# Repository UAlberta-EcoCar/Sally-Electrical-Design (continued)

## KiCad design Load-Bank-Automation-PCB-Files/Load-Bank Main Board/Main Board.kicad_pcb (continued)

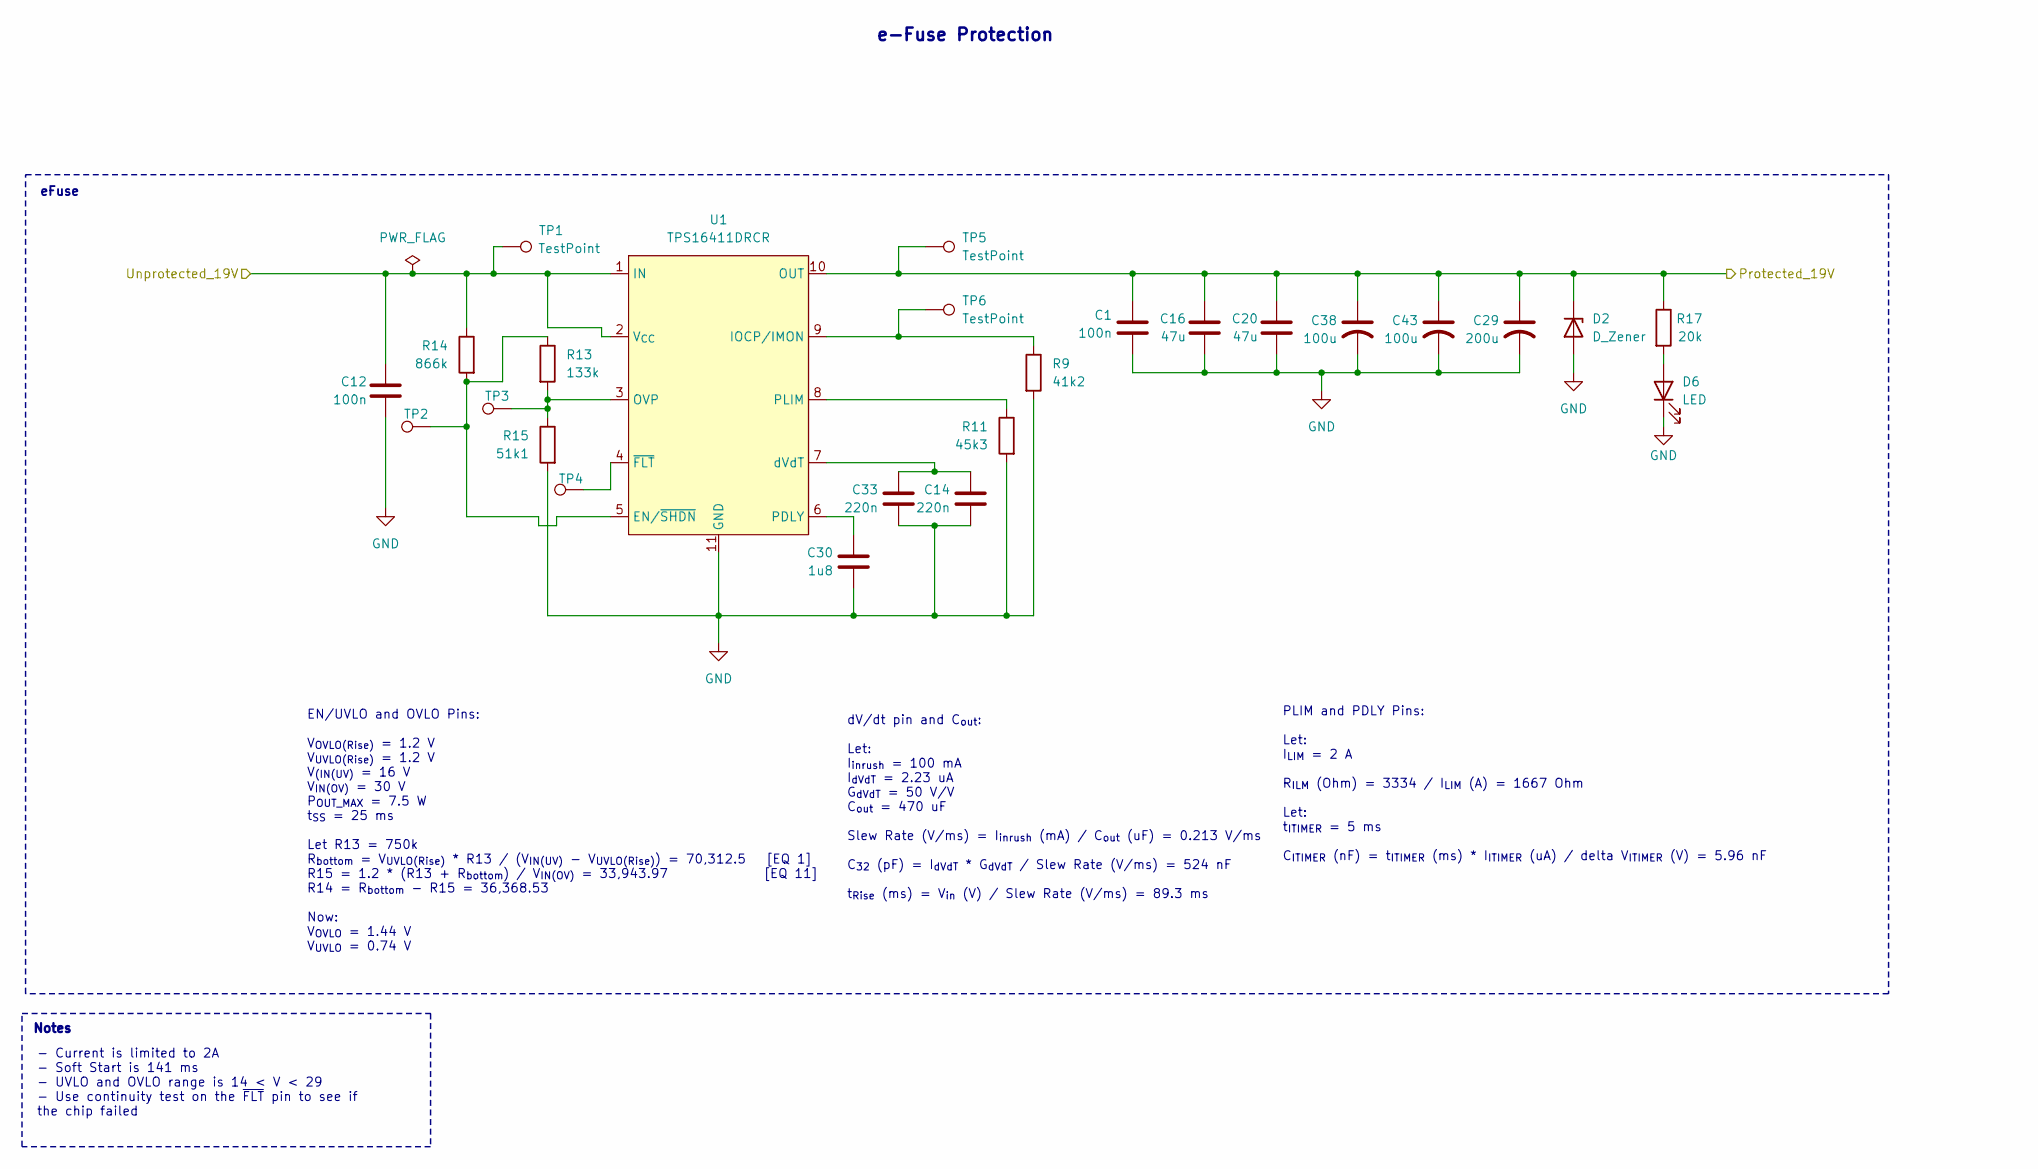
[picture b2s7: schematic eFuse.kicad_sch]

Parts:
C1, C12: 100n; C_0603_1608Metric_Pad1.08x0.95mm_HandSolder
C14, C33: 220n; C_0603_1608Metric_Pad1.08x0.95mm_HandSolder
C16, C20: 47u; C_1206_3216Metric_Pad1.33x1.80mm_HandSolder
C29: 200u; CP_Radial_D8.0mm_P3.50mm
C30: 1u8; C_1206_3216Metric_Pad1.33x1.80mm_HandSolder
C38, C43: 100u; CP_Radial_D8.0mm_P3.50mm
D2: D_Zener; D_TUMD2
D6: LED; LED_0603_1608Metric
R9: 41k2; R_0603_1608Metric_Pad0.98x0.95mm_HandSolder
R11: 45k3; R_0603_1608Metric_Pad0.98x0.95mm_HandSolder
R13: 133k; R_0603_1608Metric_Pad0.98x0.95mm_HandSolder
R14: 866k; R_0603_1608Metric_Pad0.98x0.95mm_HandSolder
R15: 51k1; R_0603_1608Metric_Pad0.98x0.95mm_HandSolder
R17: 20k; R_0603_1608Metric_Pad0.98x0.95mm_HandSolder
TP1, TP2, TP3, TP4, TP5, TP6: TestPoint; TestPoint_Pad_D1.0mm
U1: TPS16411DRCR; VSON-10-1EP_3x3mm_P0.5mm_EP1.65x2.4mm_ThermalVias

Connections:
/Main_Power/DC-DC Buck 12V/Protected_19V: C1.1, C16.1, C20.1, C29.1, C38.1, C43.1, D2.1 (K), R17.1, TP5.1, U1.10 (OUT); also elsewhere on the board
/Main_Power/eFuse/Unprotected_19V: C12.1, R14.1, TP1.1, U1.1 (IN), U1.2 (V_{CC}); also elsewhere on the board
GND: C1.2, C12.2, C14.1, C16.2, C20.2, C29.2, C30.1, C33.1, C38.2, C43.2, D2.2 (A), D6.1 (K), R9.2, R11.2, R15.2, U1.11 (GND); also elsewhere on the board
unnamed: D6.2 (A), R17.2
unnamed: R13.1, R14.2, TP2.1, U1.5 (EN/~SHDN)
unnamed: R9.1, TP6.1, U1.9 (IOCP/IMON)
unnamed: R13.2, R15.1, TP3.1, U1.3 (OVP)
unnamed: C30.2, U1.6 (PDLY)
unnamed: R11.1, U1.8 (PLIM)
unnamed: C14.2, C33.2, U1.7 (dVdT)
unnamed: TP4.1, U1.4 (~FLT)

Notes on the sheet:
PLIM and PDLY Pins: Let: I_{LIM} = 2 A R_{ILM} (Ohm) = 3334 / I_{LIM} (A) = 1667 Ohm Let: t_{ITIMER} = 5 ms C_{ITIMER} (nF) = t_{ITIMER} (ms) * I_{ITIMER} (uA) / delta V_{ITIMER} (V) = 5.96 nF
Notes
EN/UVLO and OVLO Pins: V_{OVLO(Rise)} = 1.2 V V_{UVLO(Rise)} = 1.2 V V_{(IN(UV)} = 16 V V_{IN(OV)} = 30 V P_{OUT_MAX} = 7.5 W t_{SS} = 25 ms Let R13 = 750k R_{bottom} = V_{UVLO(Rise)} * R13 / (V_{IN(UV)} - V_{UVLO(Rise)}) = 70,312.5 [EQ 1] R15 = 1.2 * (R13 + R_{bottom}) / V_{IN(OV)} = 33,943.97 [EQ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
e-Fuse Protection
- Current is limited to 2A - Soft Start is 141 ms - UVLO and OVLO range is 14 < V < 29 - Use continuity test on the ~{FLT} pin to see if the chip failed
eFuse
dV/dt pin and C_{out}: Let: I_{inrush} = 100 mA I_{dVdT} = 2.23 uA G_{dVdT} = 50 V/V C_{out} = 470 uF Slew Rate (V/ms) = I_{inrush} (mA) / C_{out} (uF) = 0.213 V/ms C_{32} (pF) = I_{dVdT} * G_{dVdT} / Slew Rate (V/ms) = 524 nF t_{Rise} (ms) = V_{in} (V) / Slew Rate (V/ms) = 89.3 ms

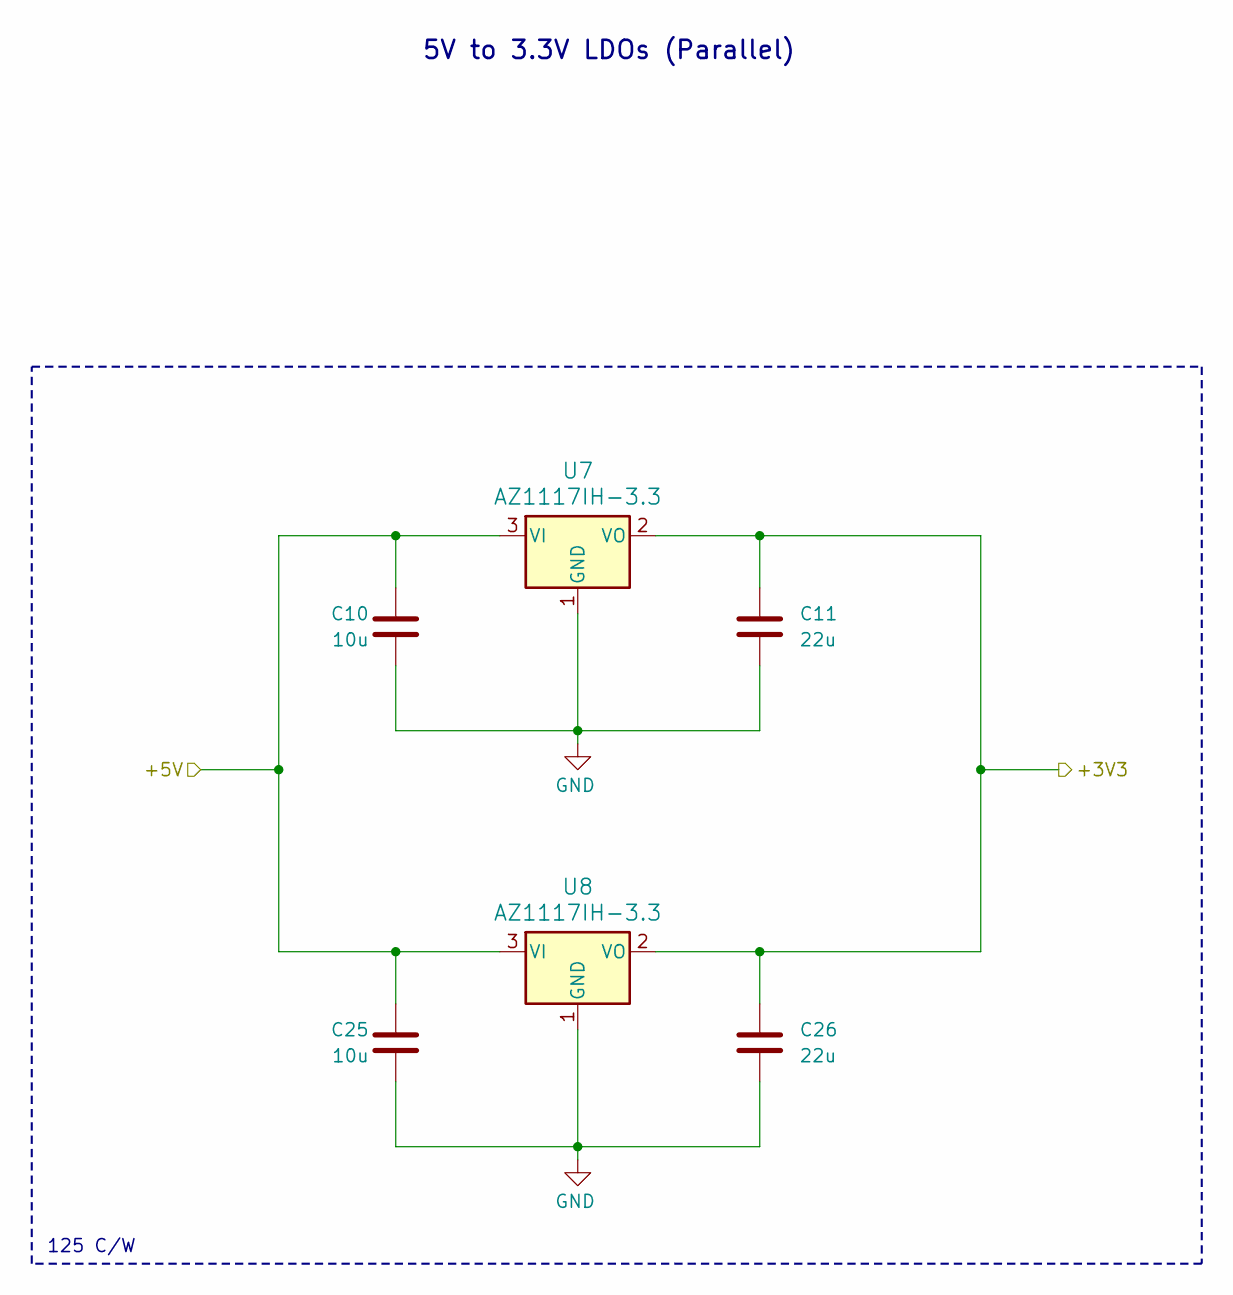
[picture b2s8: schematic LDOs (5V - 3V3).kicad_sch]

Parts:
C10, C25: 10u; C_1206_3216Metric_Pad1.33x1.80mm_HandSolder
C11, C26: 22u; C_0805_2012Metric_Pad1.18x1.45mm_HandSolder
U7, U8: AZ1117IH-3.3; SOT-223-3_TabPin2

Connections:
+5V: C10.1, C25.1, U7.3 (VI), U8.3 (VI); also elsewhere on the board
GND: C10.2, C11.2, C25.2, C26.2, U7.1 (GND), U8.1 (GND); also elsewhere on the board

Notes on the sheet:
5V to 3.3V LDOs (Parallel)
125 C/W

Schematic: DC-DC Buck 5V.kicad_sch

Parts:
C3: 3u3; C_0805_2012Metric_Pad1.18x1.45mm_HandSolder
C21, C27: 100n; C_0603_1608Metric_Pad1.08x0.95mm_HandSolder
C28: 15u; C_1210_3225Metric_Pad1.33x2.70mm_HandSolder
L2: 8u2; L_Bourns_SDR0403
R4: 750k; R_0402_1005Metric_Pad0.72x0.64mm_HandSolder
R20: 294k; R_0402_1005Metric_Pad0.72x0.64mm_HandSolder
R29: 88.7k; R_0402_1005Metric_Pad0.72x0.64mm_HandSolder
R30: 22.1k; R_0402_1005Metric_Pad0.72x0.64mm_HandSolder
TP9, TP10: TestPoint; TestPoint_Pad_D1.0mm
U4: TPS560430YQDBVRQ1; SOT-23-6

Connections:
+5V: C28.1, L2.2, R29.1, TP10.1; also elsewhere on the board
+12V: C3.1, C21.1, R4.1, U4.5 (VIN); also elsewhere on the board
GND: C3.2, C21.2, C28.2, R20.2, R30.2, U4.2 (GND); also elsewhere on the board
unnamed: C27.1, U4.1 (CB)
unnamed: R4.2, R20.1, TP9.1, U4.4 (EN)
unnamed: R29.2, R30.1, U4.3 (FB)
unnamed: C27.2, L2.1, U4.6 (SW)

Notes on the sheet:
https://webench.ti.com/appinfo/webench/scripts/SDP.cgi?ID=B7009E65DFD8AE3E
DC/DC Buck Converter
Notes
Did many caluclations by hand and confirms some values
PFM Buck Converter
V_{IN_MAX} = 36 V I_{OUT_MAX} = 600 mA t_{SS} = 1.8 ms f_{sw} = 2100 KHz

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
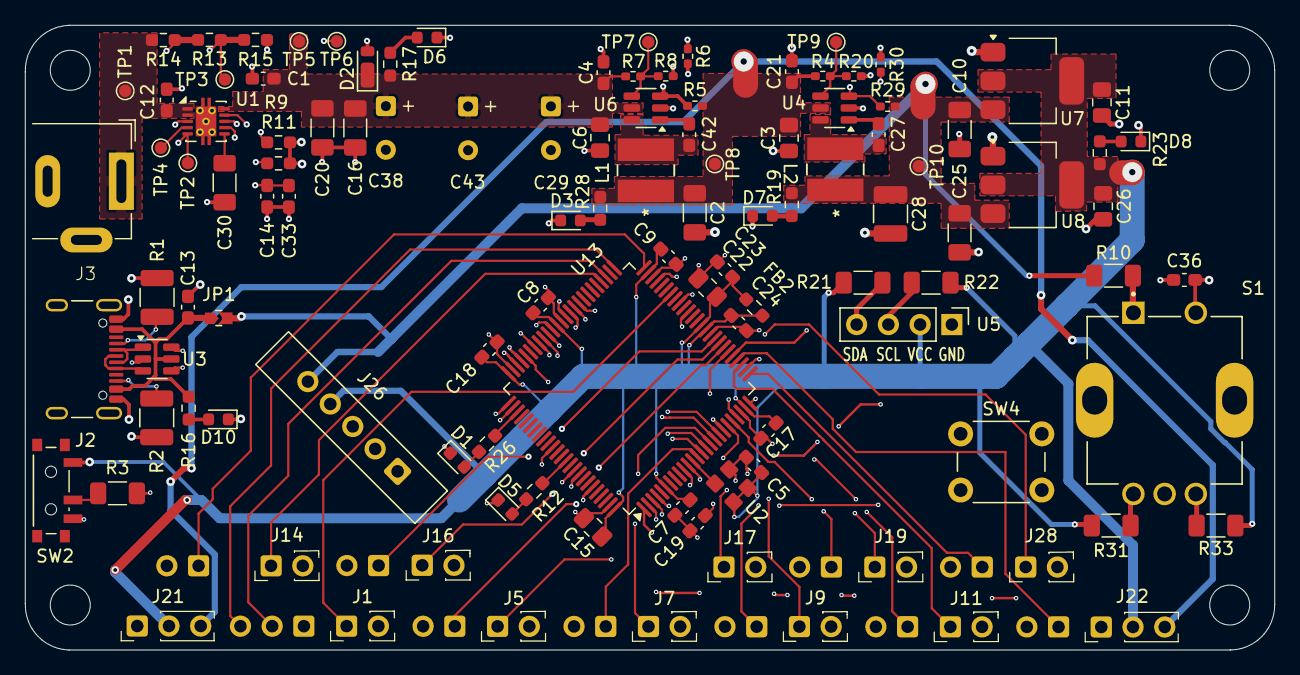
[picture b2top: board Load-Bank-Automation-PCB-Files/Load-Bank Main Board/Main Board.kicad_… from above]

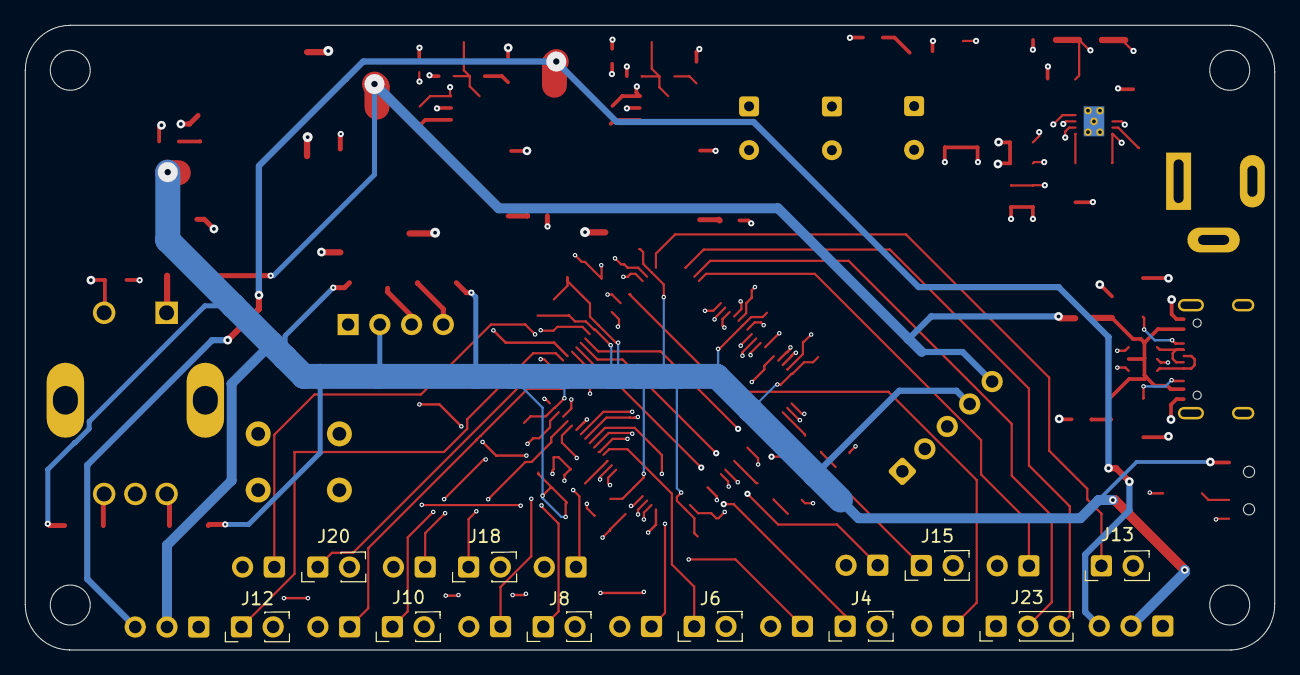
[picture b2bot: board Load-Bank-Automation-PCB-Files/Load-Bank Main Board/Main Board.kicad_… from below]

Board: 4 copper layers, 100.0 x 50.0 mm, 126 parts (10 on the bottom side), 90 nets.

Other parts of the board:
D7, D8: LED; LED_0603_1608Metric
JP1: Jumper_2_Open; J_0603_Triangular
R19, R23: 20k; R_0603_1608Metric_Pad0.98x0.95mm_HandSolder

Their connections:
+5V: JP1.2 (B), R19.2; also elsewhere on the board
GND: D7.1 (K), D8.1 (K); also elsewhere on the board
unnamed: D7.2 (A), R19.1
unnamed: D8.2 (A), R23.1
VBUS: JP1.1 (A); also elsewhere on the board

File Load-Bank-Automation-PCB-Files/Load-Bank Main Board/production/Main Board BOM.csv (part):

"Reference","Qty","Value","DNP","Exclude from BOM","Exclude from Board","Footprint","Datasheet","Description"
"C1,C4,C5,C7,C8,C9,C12,C13,C17,C18,C19,C21,C23,C24,C27,C36,C42","17","100n","","","","Capacitor_SMD:C_0603_1608Metric_Pad1.08x0.95mm_HandSolder","https://www.digikey.ca/en/products/detail/tdk-corporation/CG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","Unpolarized capacitor"
"C2","1","15u","","","","Capacitor_SMD:C_1206_3216Metric_Pad1.33x1.80mm_HandSolder","https://www.digikey.ca/en/products/detail/tdk-corporation/C3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","Unpolarized capacitor"
"C3,C6","2","3u3","","","","Capacitor_SMD:C_0805_2012Metric_Pad1.18x1.45mm_HandSolder","https://www.digikey.ca/en/products/detail/tdk-corporation/C2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","C2012X7R1V335K125AC,Unpolarized capacitor"
"C10,C25","2","10u","","","","Capacitor_SMD:C_1206_3216Metric_Pad1.33x1.80mm_HandSolder","https://www.digikey.ca/en/products/detail/tdk-corporation/C2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","C2012X5R1C106K085AC"
"C11,C26","2","22u","","","","Capacitor_SMD:C_0805_2012Metric_Pad1.18x1.45mm_HandSolder","https://www.digikey.ca/en/products/detail/nic-components-cor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","NMC0805X5R226M25TRPLPF"
"C14,C33","2","220n","","","","Capacitor_SMD:C_0603_1608Metric_Pad1.08x0.95mm_HandSolder","https://www.digikey.ca/en/products/detail/samsung-electro-me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","CL10B224KB8NNNC"
"C15,C22","2","10u","","","","Capacitor_SMD:C_0805_2012Metric_Pad1.18x1.45mm_HandSolder","https://www.digikey.ca/en/products/detail/samsung-electro-me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","Unpolarized capacitor"
"C16,C20","2","47u","","","","Capacitor_SMD:C_1206_3216Metric_Pad1.33x1.80mm_HandSolder","https://www.digikey.ca/en/products/detail/tdk-corporation/C3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","Unpolarized capacitor"
"C28","1","15u","","","","Capacitor_SMD:C_1210_3225Metric_Pad1.33x2.70mm_HandSolder","https://www.digikey.ca/en/products/detail/tdk-corporation/C3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","Unpolarized capacitor"
"C29","1","200u","","","","Capacitor_THT:CP_Radial_D8.0mm_P3.50mm","https://www.digikey.ca/en/products/detail/rubycon/35ZLH220ME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","capacitor, US symbol"
"C30","1","1u8","","","","Capacitor_SMD:C_1206_3216Metric_Pad1.33x1.80mm_HandSolder","https://www.digikey.ca/en/products/detail/kemet/C1206C185K5R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","C1206C185K5RACAUTO"
"C38,C43","2","100u","","","","Capacitor_THT:CP_Radial_D8.0mm_P3.50mm","https://www.digikey.ca/en/products/detail/nichicon/UVR1H101M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","capacitor, US symbol"
"D1,D3,D5,D6,D7,D8,D10","7","LED","","","","LED_SMD:LED_0603_1608Metric","~","Light emitting diode"
"D2","1","D_Zener","","","","Diode_SMD:D_TUMD2","https://toshiba.semicon-storage.com/info/CUHZ24V_datasheet_e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","VBR = 24 (Typ), VC = 25.5"
"FB2","1","300R","","","","Resistor_SMD:R_0603_1608Metric_Pad0.98x0.95mm_HandSolder","https://www.digikey.ca/en/products/detail/bourns-inc/MU3261-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","Ferrite bead"
"H1,H2,H3,H4","4","MountingHole","","Excluded from BOM","","MountingHole:MountingHole_3.2mm_M3","~","Mounting Hole without connection"
"J1,J4,J5,J6,J7,J8,J9,J10,J11,J12,J13,J14,J15,J16,J17,J18,J19,J20,J28","19","Conn_01x02","","","","Connector_PinHeader_1.00mm:IDC_PinHeader_1x02_P1.00mm_Vertical","~","Generic connector, single row, 01x02, script generated (kicad-library-utils/schlib/autogen/connector/)"
"J2","1","USB_C_Receptacle_USB2.0_14P","","","","Connector_USB:USB_C_Receptacle_GCT_USB4105-xx-A_16P_TopMnt_Horizontal","https://www.usb.org/sites/default/files/documents/usb_type-c.zip","USB 2.0-only 14P Type-C Receptacle connector"
"J3","1","Barrel_Jack_MountingPin","","","","Connector_BarrelJack:BarrelJack_TENSILITY_54-00130_Horizontal","https://tensility.s3.us-west-2.amazonaws.com/uploads/pdffile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","DC Barrel Jack with a mounting pin"
"J21,J22,J23","3","Conn_01x03","","","","Connector_PinHeader_1.00mm:IDC_PinHeader_1x03_P1.00mm_Vertical","~","Generic connector, single row, 01x03, script generated (kicad-library-utils/schlib/autogen/connector/)"
"J26","1","STM32-Prog-Header","","","","ecocad_lib_footprints:IDC-STM32-Prog-Header_2x05_P2.54mm_Vertical","~","Generic connector, double row, 02x05, odd/even pin numbering scheme (row 1 odd numbers, row 2 even numbers), script generated (kicad-library-utils/schlib/autogen/connector/)"
"JP1","1","Jumper_2_Open","","","","ecocad_lib_footprints:J_0603_Triangular","~","Jumper, 2-pole, open"
"L1","1","33u","","","","Inductor_SMD:L_Bourns_SDR0403","https://www.bourns.com/docs/Product-Datasheets/sdr0403.pdf","SDR0403-330KL"
"L2","1","8u2","","","","Inductor_SMD:L_Bourns_SDR0403","https://www.digikey.ca/en/products/detail/bourns-inc/SDR0403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","SDR0403-8R2ML"
"R1,R2","2","5k1","","","","Resistor_SMD:R_1210_3225Metric_Pad1.30x2.65mm_HandSolder","https://www.digikey.ca/en/products/detail/yageo/RC1210FR-075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","Resistor"
"R3,R10,R21,R22,R31,R33","6","4k7","","","","Resistor_SMD:R_1206_3216Metric_Pad1.30x1.75mm_HandSolder","https://www.digikey.ca/en/products/detail/yageo/RC1206FR-074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","Resistor"
"R4","1","750k","","","","Resistor_SMD:R_0402_1005Metric_Pad0.72x0.64mm_HandSolder","https://www.digikey.ca/en/products/detail/vishay-dale/CRCW04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","CRCW0402750KFKED"
"R5","1","243k","","","","Resistor_SMD:R_0402_1005Metric_Pad0.72x0.64mm_HandSolder","https://www.digikey.ca/en/products/detail/vishay-dale/CRCW04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","Resistor"
"R6,R30","2","22.1k","","","","Resistor_SMD:R_0402_1005Metric_Pad0.72x0.64mm_HandSolder","https://www.digikey.ca/en/products/detail/vishay-dale/CRCW04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","Resistor"
"R7","1","1.37M","","","","Resistor_SMD:R_0402_1005Metric_Pad0.72x0.64mm_HandSolder","https://www.digikey.ca/en/products/detail/vishay-dale/CRCW04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","CRCW04021M37FKED"
"R8","1","191k","","","","Resistor_SMD:R_0402_1005Metric_Pad0.72x0.64mm_HandSolder","https://www.digikey.ca/en/products/detail/vishay-dale/CRCW04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","CRCW0402191KFKED"
"R9","1","41k2","","","","Resistor_SMD:R_0603_1608Metric_Pad0.98x0.95mm_HandSolder","https://www.digikey.ca/en/products/detail/yageo/RC0603FR-074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","RC0603FR-0741K2L"
"R11","1","45k3","","","","Resistor_SMD:R_0603_1608Metric_Pad0.98x0.95mm_HandSolder","https://www.digikey.ca/en/products/detail/yageo/RC0603FR-074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","RC0603FR-0745K3L"
"R12,R16,R17,R19,R23,R26,R28","7","20k","","","","Resistor_SMD:R_0603_1608Metric_Pad0.98x0.95mm_HandSolder","https://www.digikey.ca/en/products/detail/yageo/RC0603FR-072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","Resistor"
"R13","1","133k","","","","Resistor_SMD:R_0603_1608Metric_Pad0.98x0.95mm_HandSolder","https://www.digikey.ca/en/products/detail/panasonic-electron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","ERA-3AEB1333V"
"R14","1","866k","","","","Resistor_SMD:R_0603_1608Metric_Pad0.98x0.95mm_HandSolder","https://www.digikey.ca/en/products/detail/panasonic-electron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","ERJ-3EKF8663V"
"R15","1","51k1","","","","Resistor_SMD:R_0603_1608Metric_Pad0.98x0.95mm_HandSolder","https://www.digikey.ca/en/products/detail/koa-speer-electron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","RK73H1JTTD5112F"
"R20","1","294k","","","","Resistor_SMD:R_0402_1005Metric_Pad0.72x0.64mm_HandSolder","https://www.digikey.ca/en/products/detail/vishay-dale/CRCW04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","CRCW0402294KFKED"
"R29","1","88.7k","","","","Resistor_SMD:R_0402_1005Metric_Pad0.72x0.64mm_HandSolder","https://www.digikey.ca/en/products/detail/vishay-dale/CRCW04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","CRCW040288K7FKED"
"S1","1","PEC12R-4220F-S0024","","","","Rotatory_Encoder_PEC12R-4220F-S0024:XDCR_PEC12R-4220F-S0024","https://www.bourns.com/docs/Product-Datasheets/PEC12R.pdf",""
"SW2","1","SW_SPDT","","","","Button_Switch_SMD:SW_SPDT_PCM12","~","Switch, single pole double throw"
"SW4","1","RESET","","","","Button_Switch_THT:SW_PUSH_6mm","~","Push button switch, generic, two pins"
"TP1,TP2,TP3,TP4,TP5,TP6,TP7,TP8,TP9,TP10","10","TestPoint","","","","TestPoint:TestPoint_Pad_D1.0mm","~","test point"
"U1","1","TPS16411DRCR","","","","Package_SON:VSON-10-1EP_3x3mm_P0.5mm_EP1.65x2.4mm_ThermalVias","https://www.ti.com/lit/ds/symlink/tps1641.pdf?ts=16987638816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","4.5 V to 40 V and 2-W to 64-W power limiting"
"U2","1","OXETDLJANF-8MHz","","","","Oscillator:OXETDLJANF-8MHz","https://www.lcsc.com/datasheet/C558766.pdf",""
"U3","1","USBLC6-2SC6","","","","Package_TO_SOT_SMD:SOT-23-6","https://www.st.com/resource/en/datasheet/usblc6-2.pdf","Very low capacitance ESD protection diode, 2 data-line, SOT-23-6"
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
